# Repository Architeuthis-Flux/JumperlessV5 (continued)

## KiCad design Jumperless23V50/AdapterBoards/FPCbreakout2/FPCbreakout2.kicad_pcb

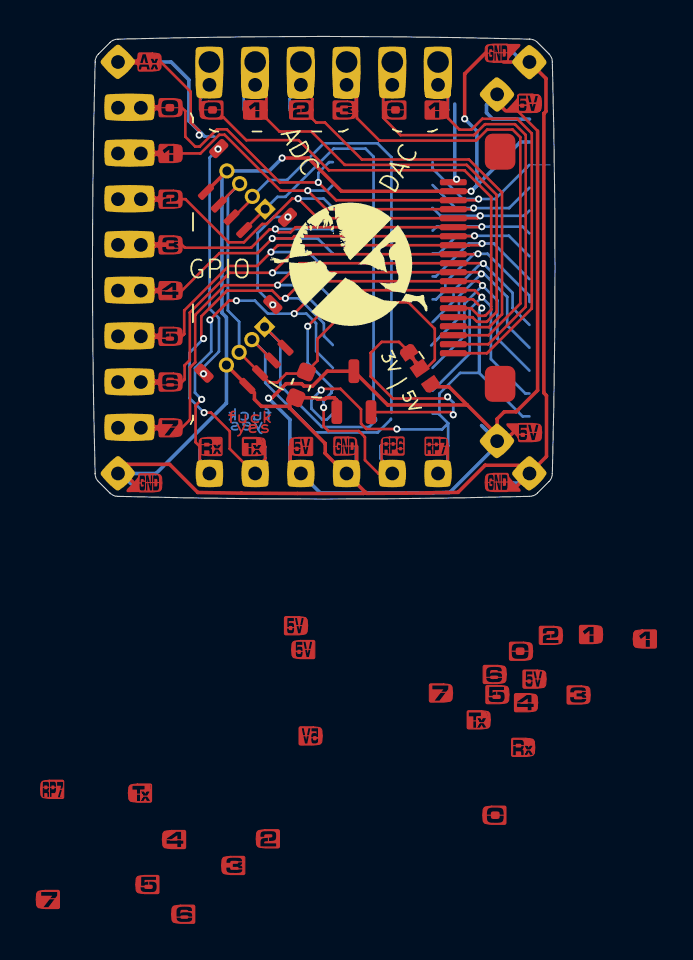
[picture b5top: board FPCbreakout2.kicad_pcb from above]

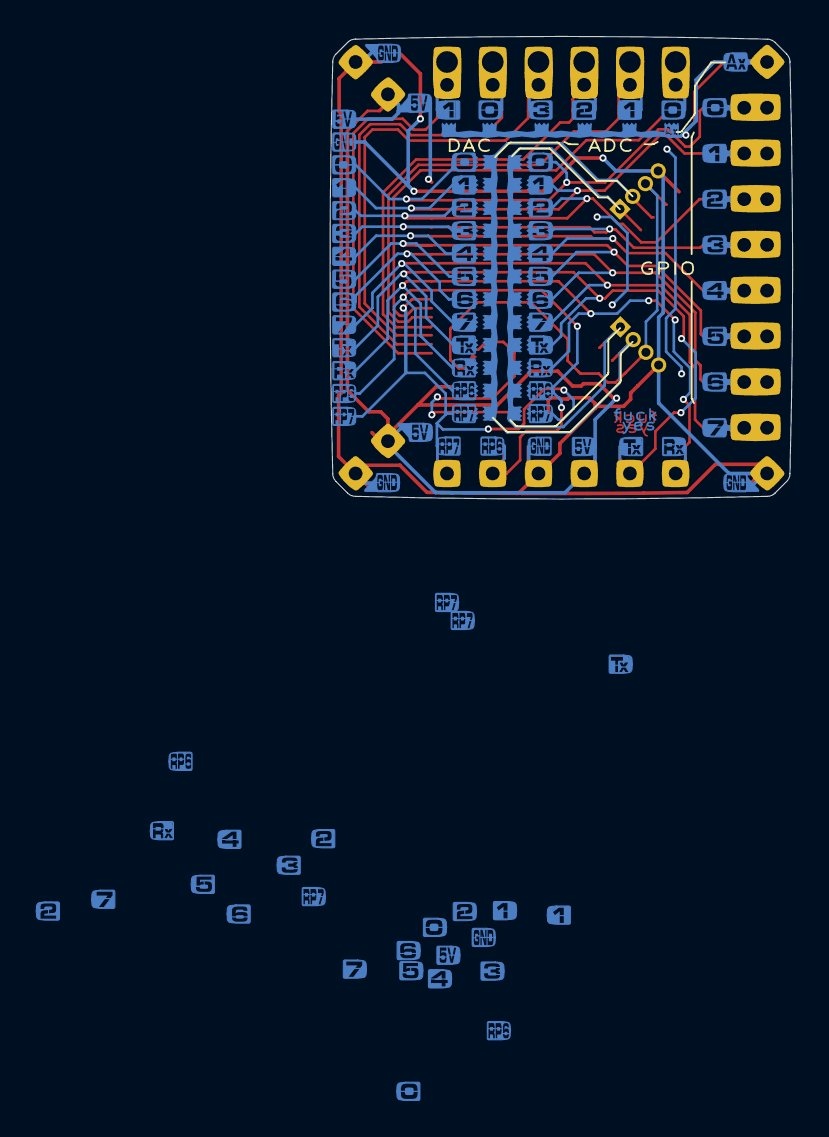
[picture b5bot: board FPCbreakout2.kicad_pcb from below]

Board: 2 copper layers, 25.7 x 25.7 mm, 20 parts (2 on the bottom side), 24 nets.

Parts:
C1: 1uF; C_0603_1608Metric
J1: FPC Connector; FPC FC05-S20FCT
J2: Routable GPIO; Conn_1x8
J3: DaisyChain_IN; daisychainRIGHT
J5, J14, J15: Power; Conn_1x2
J6: Control_I2C; Conn_1x2
J7: DACs; Conn_1x2
J8: ADCs; Conn_1x4
J9: Bus Pirate; Conn_1x10
J10: Routable UART; Conn_1x2
J17, J18: Conn_01x04; QwiicSMD
J20, J20#2: Conn_01x04; PinHeader_1x04_P1.00mm_Vertical
JP1: SolderJumper_3_Bridged12; SolderJumper-3_P1.3mm_Bridged12_Pad1.0x1.5mm
U1: SolderJumper_4of1_small
U3: Qwiic_Selector
U4: XC6206PxxxMR; SOT-23-3

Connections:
+5V: J1.1, J3.1, J5.1, J14.1, J15.1, JP1.3 (B), U4.3 (VI)
ADC_UNBUFFERED_+-8V_0: J1.15, J8.1
ADC_UNBUFFERED_+-8V_1: J1.16, J8.2
ADC_UNBUFFERED_+-8V_2: J1.17, J8.3
ADC_UNBUFFERED_+-8V_3: J1.18, J8.4
DAC_0: J1.19, J7.1
DAC_1: J1.20, J7.2
GND: C1.2, J1.2, J3.2, J5.2, J9.10, J14.2, J15.2, J17.4, J18.4, J20.4, J20#2.4, U4.1 (GND)
GPIO_6: J1.13, J3.13, J6.1, U3.13 (RP6)
GPIO_7: J1.14, J3.14, J6.2, U3.14 (RP7)
GPIO_20: J1.3, J2.1, J3.3, U3.3 (0)
GPIO_21: J1.4, J2.2, J3.4, U3.4 (1)
GPIO_22: J1.5, J2.3, J3.5, U3.5 (2)
GPIO_23: J1.6, J2.4, J3.6, U3.6 (3)
GPIO_24: J1.7, J2.5, J3.7, U3.7 (4)
GPIO_25: J1.8, J2.6, J3.8, U3.8 (5)
GPIO_26: J1.9, J2.7, J3.9, U3.9 (6)
GPIO_27: J1.10, J2.8, J3.10, U3.10 (7)
unnamed: J17.1, J18.1, J20.1, J20#2.1, U3.2 (SCL), U3.16 (SCL)
unnamed: J17.2, J18.2, J20.2, J20#2.2, U3.1 (SDA), U3.17 (SDA)
unnamed: JP1.1 (A), U4.2 (VO)
Qwiic_Power: C1.1, J17.3, J18.3, J20.3, J20#2.3, JP1.2 (C)
UART_Rx: J1.12, J3.12, J10.2, U3.12 (Rx)
UART_Tx: J1.11, J3.11, J10.1, U3.11 (Tx)

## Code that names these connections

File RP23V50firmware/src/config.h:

#ifndef CONFIG_H
#define CONFIG_H

//Jumperless config
#include "JumperlessDefines.h"


// extern int hwRevision;
// extern int probeRevision;


extern struct config jumperlessConfig;
// Forward declarations of nested structs
struct hardware;
struct dacs;
struct debug;
struct routing;
struct calibration;
struct logo_pads;
struct display_settings;
struct gpio;
struct serial_1;
struct serial_2;
struct top_oled;

struct config {
    struct hardware {
        int generation = 5;
        int revision = 5;
        int probe_revision = 5;
    } hardware;

    struct dacs {
        float top_rail = 0.00;
        float bottom_rail = 0.00;
        float dac_0 = 3.33;
        float dac_1 = 0.00;
        bool set_dacs_on_boot = false;
        bool set_rails_on_boot = true;
        int probe_power_dac = 0;
        float limit_max = 8.00;
        float limit_min = -8.00;
    } dacs;

    struct debug {
        bool file_parsing = false;
        bool net_manager = false;
        bool nets_to_chips = false;
        bool nets_to_chips_alt = false;
        bool leds = false;
        bool probing = false;
        bool oled = false;
        bool logo_pads = false;
        bool logic_analyzer = true; 
        int  arduino = 0;
    } debug;

    struct routing {
        int stack_paths = 2;
        int stack_rails = 3;
        int stack_dacs = 0;
        int rail_priority = 1;
    } routing;

    struct calibration {
        int top_rail_zero = 1650;
        float top_rail_spread = 21.5;
        int bottom_rail_zero = 1650;
        float bottom_rail_spread = 21.5;
        int dac_0_zero = 1650;
        float dac_0_spread = 21.5;
        int dac_1_zero = 1650;
        float dac_1_spread = 21.5;
        float adc_0_zero = 9.0;
        float adc_0_spread = 18.28;
        float adc_1_zero = 9.0;
        float adc_1_spread = 18.28;
        float adc_2_zero = 9.0;
        float adc_2_spread = 18.28;
        float adc_3_zero = 9.0;
        float adc_3_spread = 18.28;
        float adc_4_zero = 0.0;
        float adc_4_spread = 5.0;
        float adc_7_zero = 9.0;
        float adc_7_spread = 18.28;
        int probe_max = 4060;
        int probe_min = 15;
        // Hysteresis thresholds to prevent oscillation between modes
        // Switch to SELECT mode when current > high threshold
        // Switch to MEASURE mode when current < low threshold
        float probe_switch_threshold_high = 0.35;  // mA - switch to SELECT
        float probe_switch_threshold_low = 0.10;   // mA - switch to MEASURE
        float probe_switch_threshold = 0.40;       // DEPRECATED - kept for backward compatibility
        float measure_mode_output_voltage = 3.30;
        float probe_current_zero = 2.0;
    } calibration;

    struct logo_pads {
        int top_guy = 0; // 0 = uart tx, 1 = uart rx, others as I think of them
        int bottom_guy = 1;
        int building_pad_top = -1;
        int building_pad_bottom = -1;
        int repeat_ms = 100;
    } logo_pads;

    struct display {
        volatile int lines_wires = 1;
        int menu_brightness = -10;
        int led_brightness = 10;
        int rail_brightness = 55;
        int special_net_brightness = 20;
        int net_color_mode = 0;
        int dump_leds = -1;
        int dump_format = 0;
        int terminal_line_buffering = 0;
    } display;

    struct gpio {
        
        ///@param 1 = input 0 = output
        int direction[10] = {
            1, //gpio_0 1 = input 0 = output
            1, //gpio_1
            1, //gpio_2
            1, //gpio_3
            1, //gpio_4
            1, //gpio_5
            1, //gpio_6
            1, //gpio_7
            0, //uart_tx
            1, //uart_rx
        };
        
        ///@param 0 = pull down 1 = pull up 2 = none 3 = bus keeper
        int pulls[10] = {
            0, //gpio_0 0 = pull down 1 = pull up 2 = none 3 = bus keeper
            0, //gpio_1
            0, //gpio_2
            0, //gpio_3
            0, //gpio_4
            0, //gpio_5
            0, //gpio_6
            0, //gpio_7
            2, //uart_tx - no pull
            2, //uart_rx - no pull
        };
        float pwm_frequency[10] = { 
            1.0, //gpio_0 default frequency in Hz 
            1.0, //gpio_1 
            1.0, //gpio_2 
            1.0, //gpio_3 
            1.0, //gpio_4 
            1.0, //gpio_5 
            1.0, //gpio_6 
            1.0, //gpio_7 
            1.0, //uart_tx 
            1.0, //uart_rx 
        }; 
        float pwm_duty_cycle[10] = {
            0.5, //gpio_0 default duty cycle (0.0 to 1.0)
            0.5, //gpio_1
            0.5, //gpio_2
            0.5, //gpio_3
            0.5, //gpio_4
            0.5, //gpio_5
            0.5, //gpio_6
            0.5, //gpio_7
            0.5, //uart_tx
            0.5, //uart_rx
        };
        bool pwm_enabled[10] = {
            false, //gpio_0 PWM enabled flag
            false, //gpio_1
            false, //gpio_2
            false, //gpio_3
            false, //gpio_4
            false, //gpio_5
            false, //gpio_6
            false, //gpio_7
            false, //uart_tx
            false, //uart_rx
        };
        // int uart_tx_pin = 0;
        // int uart_rx_pin = 1;
        // int uart_tx_pull = 2;
        // int uart_rx_pull = 2;
        int uart_tx_function = 0; //0 = tx, 1 = rx, 2 = gpio_in, 3 = gpio_out
        int uart_rx_function = 1;
    } gpio;

    
        struct serial_1 {
            int function = 1; 
            int baud_rate = 115200;
            int print_passthrough = 0;
            int connect_on_boot = 0;
            int lock_connection = 0;
            int autoconnect_flashing = 1;
            bool async_passthrough = true;
        } serial_1;

        
        struct serial_2 {
            int function = 0; // 0 = off
            int baud_rate = 115200;
            int print_passthrough = 0;
            int connect_on_boot = 0;
            int lock_connection = 0;
            int autoconnect_flashing = 0;
        } serial_2;

        struct top_oled {
            int enabled = 0;
            int i2c_address = 0x3C;
            int width = 128;
            int height = 32;
            int sda_pin = 26;//the actual hardware pin number
            int scl_pin = 27;//the actual hardware pin number
            int gpio_sda = RP_GPIO_26; //the define number for the hardware pin
            int gpio_scl = RP_GPIO_27; //the define number for the hardware pin
            int sda_row = NANO_D2; //the row number
            int scl_row = NANO_D3; //the row number
            int connect_on_boot = 0;
            int lock_connection = 0;
            int autoconnect_check_interval = -1;
            int font = 1;
            int show_in_terminal = 0;
        } top_oled;
    
};

#endif // CONFIG_H

/*
 if (EEPROM.read(FIRSTSTARTUPADDRESS) != 0xAA || forceDefaults == 1) {
   EEPROM.write(FIRSTSTARTUPADDRESS, 0xAA);
   
   EEPROM.write(REVISIONADDRESS, REV);

   EEPROM.write(DEBUG_FILEPARSINGADDRESS, 0);
   EEPROM.write(TIME_FILEPARSINGADDRESS, 0);
   EEPROM.write(DEBUG_NETMANAGERADDRESS, 0);
   EEPROM.write(TIME_NETMANAGERADDRESS, 0);
   EEPROM.write(DEBUG_NETTOCHIPCONNECTIONSADDRESS, 0);
   EEPROM.write(DEBUG_NETTOCHIPCONNECTIONSALTADDRESS, 0);
   EEPROM.write(DEBUG_LEDSADDRESS, 0);
   EEPROM.write(LEDBRIGHTNESSADDRESS, DEFAULTBRIGHTNESS);
   EEPROM.write(RAILBRIGHTNESSADDRESS, DEFAULTRAILBRIGHTNESS);
   EEPROM.write(SPECIALBRIGHTNESSADDRESS, DEFAULTSPECIALNETBRIGHTNESS);
   EEPROM.write(PROBESWAPADDRESS, 0);
   EEPROM.write(ROTARYENCODER_MODE_ADDRESS, 0);
   EEPROM.write(DISPLAYMODE_ADDRESS, 1);
   EEPROM.write(NETCOLORMODE_ADDRESS, 0);
   EEPROM.write(MENUBRIGHTNESS_ADDRESS, 100);
   EEPROM.write(PATH_DUPLICATE_ADDRESS, 2);
   EEPROM.write(DAC_DUPLICATE_ADDRESS, 0);
   EEPROM.write(POWER_DUPLICATE_ADDRESS, 2);
   EEPROM.write(DAC_PRIORITY_ADDRESS, 1);
   EEPROM.write(POWER_PRIORITY_ADDRESS, 1);
   EEPROM.write(SHOW_PROBE_CURRENT_ADDRESS, 0);

   saveVoltages(0.0f, 0.0f, 3.33f, 0.0f);

*/

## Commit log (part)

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2024-05-22 Changed caps on rail power supplies
2024-05-22 ignore stuff
2024-06-02 Still fucking around, nothing works
2024-06-06 Onboard Menu, some general organizing
2024-06-08 Lowercase numbers
2024-06-08 Update README.md to let people know that it's for the current model Jumperless
2024-06-12 Hammering away on onboard menus
2024-06-12 Add a bunch of random videos
2024-06-16 Add Crowd Supply Draft
2024-06-16 ModBadger Edits
2024-07-07 menus inside menus
2024-07-09 Added 3D board shell files
2024-07-25 Add videos to README.md
2024-07-26 Hackin' away at shit
2024-08-21 Fixed lockups - added Apps to Menu - routed 23V50
2024-08-22 Fix typo (breaboard), consistently capitalize X-ray
2024-08-24 update revision number
2024-08-24 newb ranch
2024-08-24 Making sure I know wtf I'm doing
2024-08-25 Got this shit mostly running on a single core
2024-08-27 Not actually single threaded
2024-08-30 Still not single core, probably never will be
2024-08-31 Start messing around with documentation
2024-08-31 parse markdown
2024-08-31 fucking with modules
2024-08-31 fuck
2024-09-01 index.md
2024-09-01 myst
2024-09-01 campaign body
2024-09-02 add new campaign-body
2024-09-03 html stuff
2024-09-03 getting into myst
2024-09-03 site fixes
2024-09-03 things
2024-09-08 squishing bugs
2024-09-08 clean up garbage
2024-09-13 add license
2024-09-15 add tag
2024-10-22 add updates
2024-10-22 little i
2024-10-26 Added UART to probing, 2nd Serial Port, Removed some legacy garbage, went back to TinyUSB
2024-10-26 fixed voltage scaling
2024-10-26 Update firmware version number (and test Discord webhook)
2024-10-27 reinit Serial1 after checking probe current
2024-10-27 Rails now set to what they were at startup
2024-10-27 moved Serial1 stuff to ArduinoStuff.cpp
2024-10-27 messing with arduino flashing stuff
2024-10-28 Cleaned DTR/Reset Handling
2024-10-28 Updated DTR and added RTS
    DTR = GPIO2
    RTS = GPIO1
2024-10-28 removed a print
2024-10-29 added first half of week 5 update
2024-10-29 USBSer2
2024-10-29 make gpio5-8 routable
2024-10-29 finished week 5 update
2024-10-30 Trigger Arduino Nano ESP32 Boot pin correctly
2024-11-06 Add week 6 update
2024-11-18 Add FPC breakout and almost finished V5r4
2024-11-20 routed V5r4
2024-11-21 pre-production revision
2025-01-12 Add post campaign update draft
2025-01-19 Added Persistent revision Defines, Started a calibration function (trigger it with $ for now)
2025-01-20 Calibrates all 4 DACs now and saves the values in flash
2025-01-23 Cleaned/sped up probe current measurement, fixed the inability to switch to slot 0 (duh), screwed around with my ghetto mutex
2025-01-23 deleted older firmware so it's less confusing
2025-01-26 Fills unused paths with redundant connections for lower on resistance
2025-02-01 Make paths disconnect without blinking everything off, added routing/stacking options menu, fixed random stuff
2025-02-01 Made the "only update new paths" thing work (I hope), Added probe current debug flag
2025-02-03 No longer need a trailing comma, made like a million things less wonky, print arbitrary text with #text (if it's longer than 14 chars it'll scroll)
2025-02-03 Made menu actually reflect options (I will change these), Calibrate and Scan work from apps menu, added Apps.cpp, added yes/no menu.
2025-02-26 add r6 schematic
2025-03-01 Fived the windows app
2025-03-01 New(ish) app
2025-03-03 Work with Wokwi's new backend
2025-03-21 Cleaned up repo, minor firmware stuff
2025-03-21 exported packaging images as RGB
2025-04-09 Made a demo custom app
2025-04-09 Made a tutorial/example app that should actually help with writing your own apps
2025-04-21 Removed Readthedocs Crap
2025-04-22 Added update 8
2025-04-28 Loads config settings from a file instead of EEPROM now!
2025-04-29 fixed a bunch of little things
2025-04-30 We have a startup animation now!!
2025-05-02 omg Arduino flashing finally works, and uses the DTR lines so it shouldn't be board-specific. It took 3 days for screwing with it for me to finally realize I needed to call USBSer1.flush().
2025-05-05 Added serial connect on boot and lock config options, refreshPaths(), arduino flashing is solid
2025-05-06 added a menu option that prints the state of every crossbar switch, reduces file operations at startup for a snappier boot.
2025-05-09 Major release version, (this is what the first batch will ship with loaded) DAC limits, OLED stuff works, brightness settings fixed, config file prints in a cut/pasteable format, added logo bounce ap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
2025-05-11 added I2C scan app, added OLED support for probing, fixed a thing where config was setting probe_min and probe_max to 0 causing checkPads() to not work
2025-05-16 Color picker and net recoloring (tap a row while not making connections to highlight a net, then tap the top building pad, and pick a color, short press to zoom, hold to confirm)
2025-05-18 kinda new UI where highlighted nets are more important and you can do things directly with them, warning net animations, gpio output toggling,
2025-05-19 Added a ton of UI stuff for `idle mode` interation, persistent net coloring on the fileststem, clickwheel highlight, gpio output toggling, more animations, highlights follow nodes instead of nets,
2025-05-21 put a timer on checking for USBser1 config changes
2025-05-24 Trying out some weird shit with second serial handling by swapping which core it runs on depending on whether you're busy/waiting for input.
2025-05-25 changed to README so it shows automatically
2025-05-25 put glossary at the top
2025-05-29 We're doing some crazy stuff with github actions to package the new app atuomatically, let's see if it works
2025-05-29 packaged windows like an idiot
2025-05-30 packaged windows exe
2025-05-30 include shell scripts files in distributions
2025-05-30 okay one more time with packaged windows stuff
2025-05-30 omg gitignore
2025-05-30 fixed probe leds, config changes not reading
2025-05-30 oled support in net highlighting, unbroke some shit
2025-06-04 Fixed routing stuff, found some buffer overflows and stuff like that, put a bunch of stuff in ram back into flash where it belongs, changed #define RP2350B 1 to RP2350A 0 because that's what pico-sdk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
2025-06-05 Totally redid routing, added a dump LEDs to Serial (use `R` to turn it on)
2025-06-07 transcription, not tested
2025-06-07 fix case for bridge
2025-06-07 Rearranged file tree
2025-06-07 Communication test for XLSX GUI app
2025-06-08 Some WIP USB serial shenanigans. Probably don't treat this code as working just yet
2025-06-09 interactive mode support (for the micropython REPL), some overly complicated port function detection stuff (so the app knows about your config settings and knows which port is set to do what)
2025-06-10 Self updating app! Fixed path stacking adding an extra duplicate, `R` print LEDs to serial works again and is the same as the second serial version, less debug printing garbage
2025-06-10 Now you can package the app yourself with JumperlessAppPackager.
2025-06-10 Fix python unicode issues with windows build
    - Resolve unicode related issues with windows app build
    - Add another packagerRequirements file without Mac-only dependencies
2025-06-10 New runs of Packager
2025-06-10 Minor updates to docs
2025-06-10 Another minor doc update
2025-06-10 Minor docs update
2025-06-10 build micropython properly
2025-06-11 Get single commands to work with `>`, added ina commands
2025-06-11 Add micropython build objects to gitignore
2025-06-12 cleanup micropython build
    - Use a tagged version of micropython
    - checkout micropython into a temporary staging directory
    - move embedded stubs out of generated code and into mphalport.c
    - update docs to standardize on micropython build process
    - skip mpy-cross steps, since the embed build targets aren't cross compiling
2025-06-12 remove unused and redundant platformio.ini config
    - -DARDUINO_ARCH_RP2040 is already set in the platform config: https://github.com/maxgerhardt/platform-raspberrypi/blob/develop/boards/jumperless_v5.json
    - Remove commented out dependency config
2025-06-13 Hack fix for stdout for python
2025-06-13 idk I didn't do much
2025-06-16 Huge update to micropython, automatically imports time, os, math modules (not machine yet but I'll get there), custom types for jumperless module (gpio states print as HIGH/LOW but evaluate as True/F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
2025-06-16 Super tiny fixes to docs
2025-06-29 Added mounting as a Mass Storage class (I did a lot with the USB descriptors so now they're named correctly and should appear as /dev/cu.usbmodemJLV5port1)
2025-07-05 Fixed windows support for interactive mode and Kilo text editor, added GPIO Bus Keeper mode (with its own animation), added python examples (you need to load them in the file manager with `m` once), 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
2025-07-06 Add a bunch of stuff to gitignore
2025-07-06 Removed unwanted files marked in .gitignore
2025-07-10 We got: python syntax highlighting, inline eKilo editing in the repl with `ctrl + e`, some fixes to multiline mode (but still the ekilo editor is a milion times more stable and you should use that), 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
2025-07-12 fix integration between file manager, eKilo, and micropython, oled will reconnect if it's enabled and out unplug it and plug it back in
2025-07-12 Added PWM to micropython and stylophone example.
2025-07-14 Respond with serial info more quickly for the app to find the right port.
2025-07-16 Added jfs (jumperless file system) to micropython, got gpio_get working again (now returns FLOATING), Faster nodefile validation (it was taking like a second)
2025-07-29 Ugh still fucking with this logic analyzer shit
2025-07-30 Added slow PWM so python you can set PWM down to 0.001Hz, added stop_core2(), send_raw(), sped up CH446Q sending a ton.
2025-07-31 Some warnings about how the logic analyzer barely works
2025-08-05 Oh yes, Jumperless is a passable mixed signal logic analyzer now
2025-08-06 fixing some very minor logic analyzer stuff
2025-08-12 got logic analyzer working in slow mode (there's a limit to how low you can set clock dividers so it's a whole separate thing), fixed some tricky shit with PIO sm allocation, detect inverted DTR puls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
2025-08-15 Completely redid the logic analyzer to be waaaaay less crashy
2025-08-16 Finally got to fix an eratta E9 bug! Now it flips the input enable quickly when a gpio is measured high, which clears the lockup
2025-08-20 Fully async serial passthrough, fixed some net highlughting stuff to show I2C, PWM, UART, stopped readGPIOwithFloating() from fucking with (some) stuff, probe switch sensing now calibrates on startup.
2025-08-22 Freed up a ton of RAM from unused garbage, added JDI MIP display demo app, fixed async serial to wait for data on serial1, WIP trying to get EKilo to be more responsive
2025-08-26 Added 3D printed stands
2025-08-26 Added the stand with the probe holder
2025-08-27 Deleted some crap files to reduce red herrings
2025-08-27 "Yeah you can get a ride, just let me move sime stuff off the passenger seat"
2025-08-28 Fix case sensitivity issues for Linux
2025-08-29 Revert a change that was breaking the eKilo editor
2025-08-30 Added back Apps changes, refactoreed MAchineCommands.cpp, refactored Peripherals.cpp
2025-08-30 Fixed removed function, removed dead MachineCode
2025-09-02 moved-user-fuctions-outofmain
2025-09-02 Start Of new UI/UX
2025-09-02 Added machine module (so far just pins and uart), fixed some weirdness with switching between file manager, repl, and ekilo, added uart examples, used some extra ram for the micropython heap and stac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
2025-09-02 Opened another USB endpoint for the TUI
2025-09-02 Got some oled stuff working and redraw on connect
2025-09-03 push stuff for a merge
2025-09-06 Added wavegen (still need to integrate it with micropython)
2025-09-06 Added waveform generator micropython module
2025-09-06 Twiddled probe timing stuff
2025-09-06 Broke out PopUp, more code cleanup
2025-10-06 Tui UI/UX
2025-10-07 Added optional line buffering (defaults to off), hysteresis on the probe switch position sensing, added a font,
2025-11-01 Revise README with detailed Jumperless V5 information
    Expanded the README to provide detailed information about Jumperless V5, including its features, usage, and links to documentation.
2025-11-14 update JumperlOS submodule
2025-11-18 Update submodules
2025-11-21 update JumperlOS
2026-01-31 Add PSRAM mod files
